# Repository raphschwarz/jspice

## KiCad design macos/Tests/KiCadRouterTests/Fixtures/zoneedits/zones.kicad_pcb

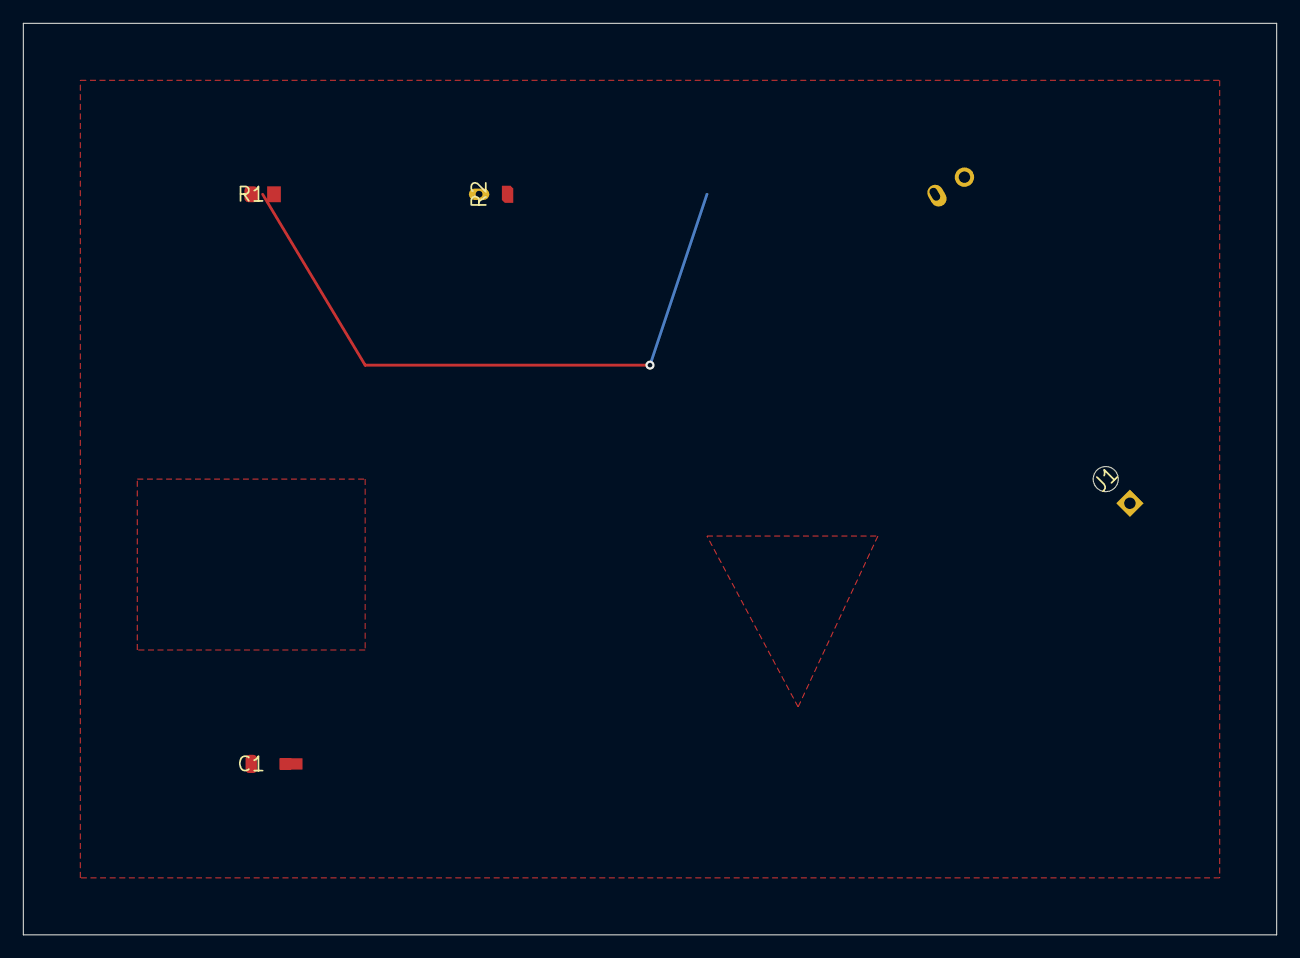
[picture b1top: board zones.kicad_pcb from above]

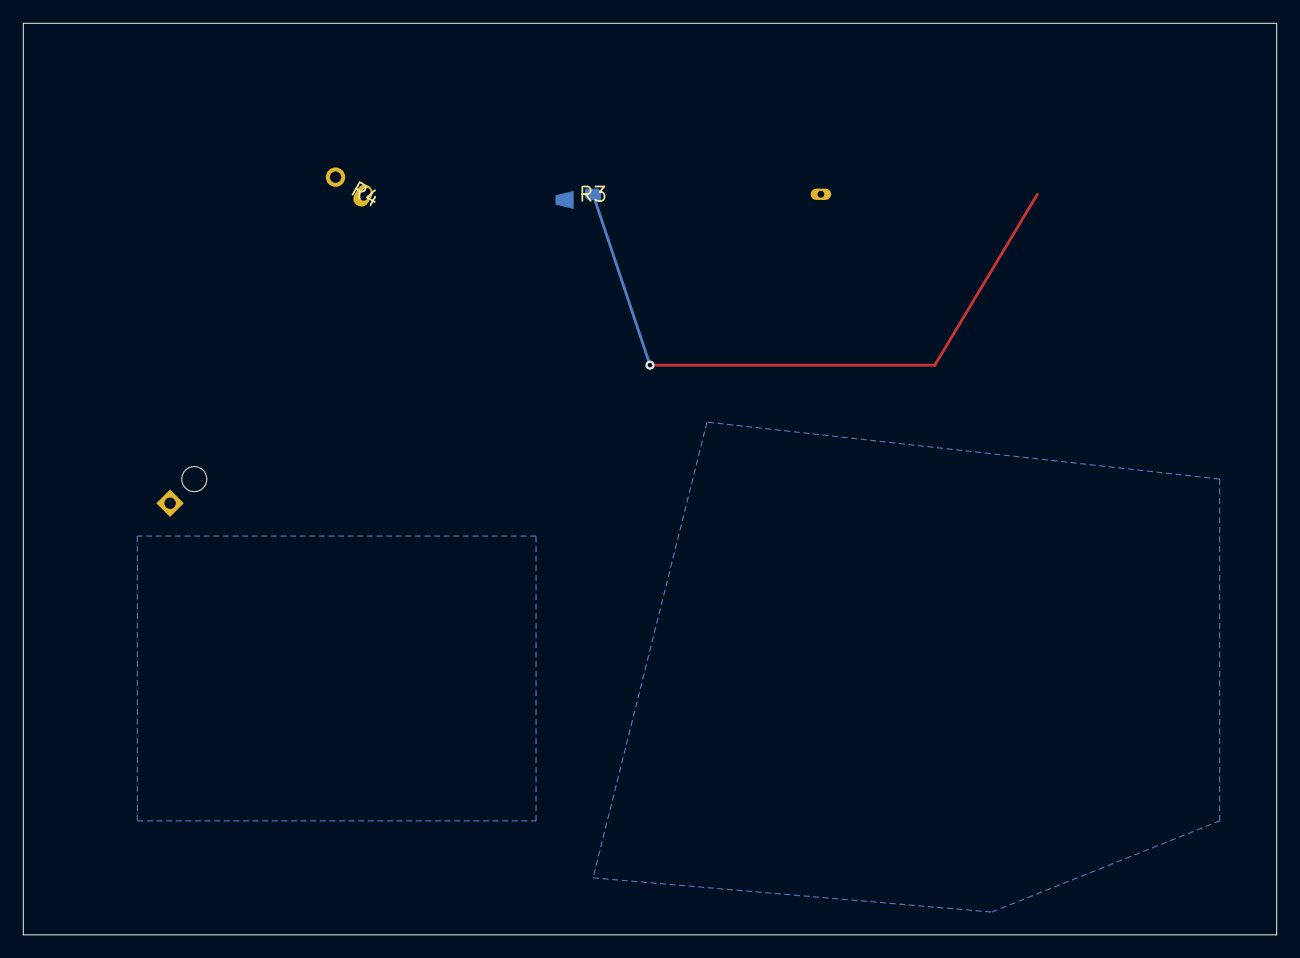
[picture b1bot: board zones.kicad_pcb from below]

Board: 4 copper layers, 110.0 x 80.0 mm, 6 parts (2 on the bottom side), 4 nets.

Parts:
C1: VC1
J1: VJ1
R1: VR1
R2: VR2
R3: VR3
R4: VR4

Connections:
CLK: C1.2, R3.2
GND: C1.1, R1.2, R2.2, R4.1
SIG: J1.1, R1.1, R3.1
VCC: R2.1, R4.2

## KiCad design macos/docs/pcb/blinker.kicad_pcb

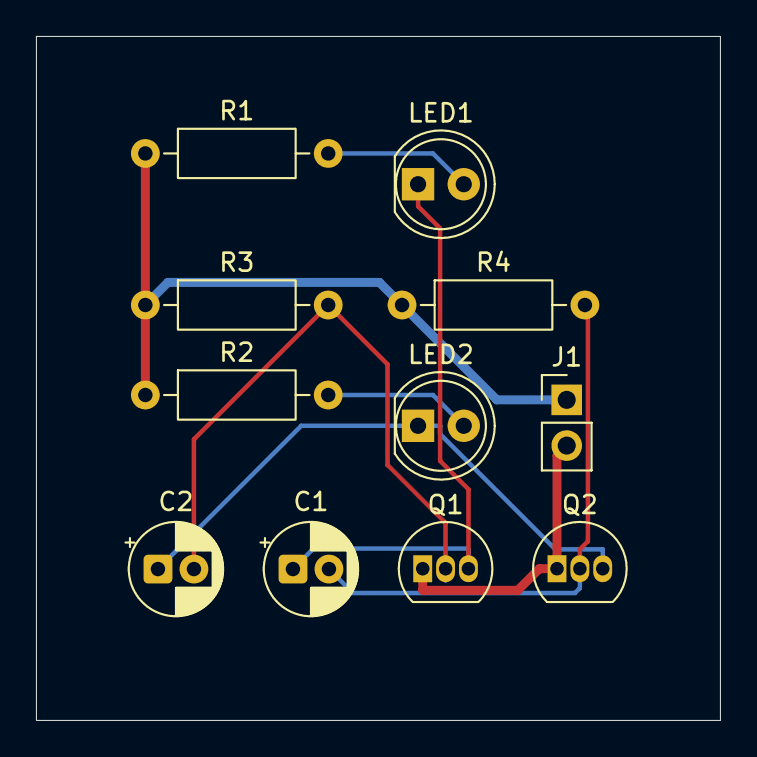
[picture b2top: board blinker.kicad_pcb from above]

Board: 2 copper layers, 38.0 x 38.0 mm, 11 parts (0 on the bottom side), 8 nets.

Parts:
C1, C2: 10u; CP_Radial_D5.0mm_P2.00mm
J1: Power 9 V; PinHeader_1x02_P2.54mm_Vertical
LED1: red LED; LED_D5.0mm
LED2: green LED; LED_D5.0mm
Q1, Q2: 2N3904; TO-92_Inline
R1, R2: 470; R_Axial_DIN0207_L6.3mm_D2.5mm_P10.16mm_Horizontal
R3: 47k; R_Axial_DIN0207_L6.3mm_D2.5mm_P10.16mm_Horizontal
R4: 51k; R_Axial_DIN0207_L6.3mm_D2.5mm_P10.16mm_Horizontal

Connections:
+9V: J1.1 (+), R1.1 (a), R2.1 (a), R3.1 (a), R4.1 (a)
GND: J1.2 (common), Q1.1 (emitter), Q2.1 (emitter)
unnamed: C1.1 (+), LED1.1 (K), Q1.3 (collector)
unnamed: C1.2 (-), Q2.2 (base), R4.2 (b)
unnamed: C2.1 (+), LED2.1 (K), Q2.3 (collector)
unnamed: C2.2 (-), Q1.2 (base), R3.2 (b)
unnamed: LED1.2 (A), R1.2 (b)
unnamed: LED2.2 (A), R2.2 (b)
